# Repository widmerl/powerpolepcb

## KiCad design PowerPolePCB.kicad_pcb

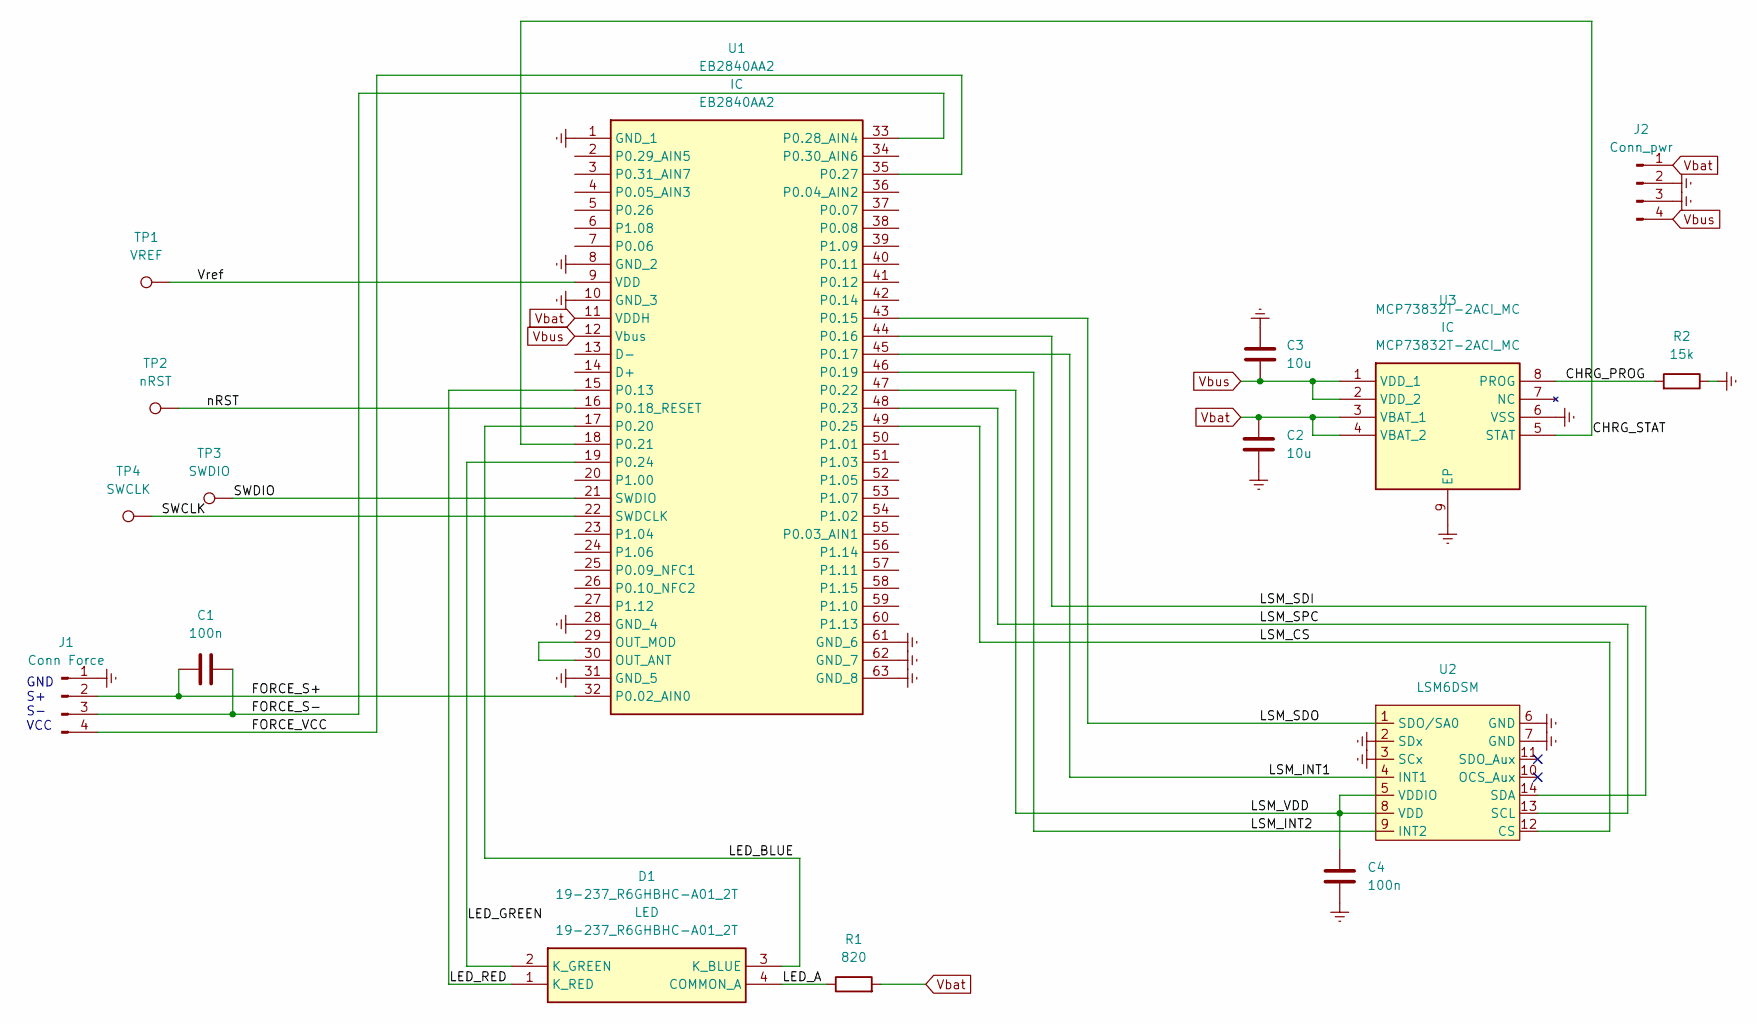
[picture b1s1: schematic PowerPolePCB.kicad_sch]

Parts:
C1, C4: 100n; C_0603_1608Metric; LCSC C14663
C2, C3: 10u; C_0603_1608Metric; LCSC C19702
D1: 19-237_R6GHBHC-A01_2T; 19237R6GHBHCA012T; Mouser Part Number 638-19237R6GHBHCA01
J1: Conn Force; PinHeader_1x04_P1.27mm_Vertical
J2: Conn_pwr; PinHeader_1x04_P1.27mm_Vertical
R1: 820; R_0603_1608Metric; LCSC C23253
R2: 15k; R_0603_1608Metric; LCSC C22809
TP1: VREF; uTP
TP2: nRST; uTP
TP3: SWDIO; uTP
TP4: SWCLK; uTP
U1: EB2840AA2; Manufacturer_Part_Number EB2840AA2
U2: LSM6DSM; LCSC C94048
U3: MCP73832T-2ACI_MC; SON50P300X200X100-9N-D; Mouser Part Number 579-MCP73832T-2ACIMC

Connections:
/CHRG_PROG: R2.2, U3.8 (PROG)
/CHRG_STAT: U1.18 (P0.21), U3.5 (STAT)
/FORCE_S+: C1.1, J1.2, U1.32 (P0.02_AIN0)
/FORCE_S-: C1.2, J1.3, U1.33 (P0.28_AIN4)
/FORCE_VCC: J1.4, U1.35 (P0.27)
/LED_A: D1.4 (COMMON_A), R1.1
/LED_BLUE: D1.3 (K_BLUE), U1.17 (P0.20)
/LED_GREEN: D1.2 (K_GREEN), U1.19 (P0.24)
/LED_RED: D1.1 (K_RED), U1.15 (P0.13)
/LSM_CS: U1.49 (P0.25), U2.12 (CS)
/LSM_INT1: U1.45 (P0.17), U2.4 (INT1)
/LSM_INT2: U1.46 (P0.19), U2.9 (INT2)
/LSM_SDI: U1.44 (P0.16), U2.14 (SDA)
/LSM_SDO: U1.43 (P0.15), U2.1 (SDO/SA0)
/LSM_SPC: U1.48 (P0.23), U2.13 (SCL)
/LSM_VDD: C4.1, U1.47 (P0.22), U2.5 (VDDIO), U2.8 (VDD)
/SWCLK: TP4.1, U1.22 (SWDCLK)
/SWDIO: TP3.1, U1.21 (SWDIO)
/Vref: TP1.1, U1.9 (VDD)
/nRST: TP2.1, U1.16 (P0.18_RESET)
Earth: C2.2, C3.1, C4.2, J1.1, J2.2, J2.3, R2.1, U1.1 (GND_1), U1.8 (GND_2), U1.10 (GND_3), U1.28 (GND_4), U1.31 (GND_5), U1.61 (GND_6), U1.62 (GND_7), U1.63 (GND_8), U2.2 (SDx), U2.3 (SCx), U2.6 (GND), U2.7 (GND), U3.6 (VSS), U3.9 (EP)
unnamed: U1.29 (OUT_MOD), U1.30 (OUT_ANT)
Vbat: C2.1, J2.1, R1.2, U1.11 (VDDH), U3.3 (VBAT_1), U3.4 (VBAT_2)
Vbus: C3.2, J2.4, U1.12 (Vbus), U3.1 (VDD_1), U3.2 (VDD_2)

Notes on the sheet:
GND S+ S- VCC

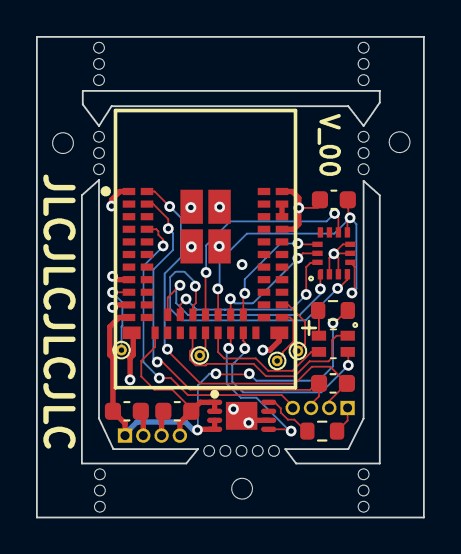
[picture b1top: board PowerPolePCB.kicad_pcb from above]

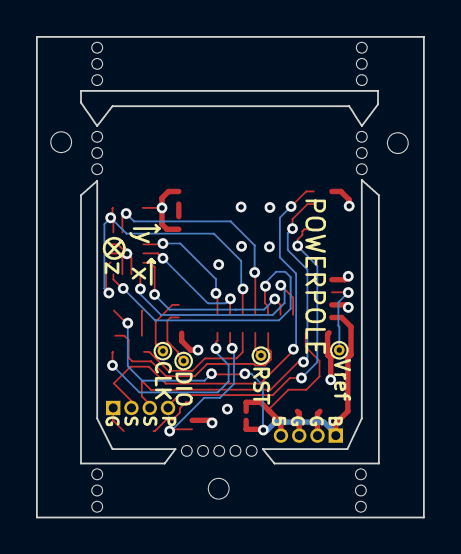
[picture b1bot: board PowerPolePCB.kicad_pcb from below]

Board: 4 copper layers, 21.5 x 26.7 mm, 26 parts (4 on the bottom side), 24 nets.

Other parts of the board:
MB1, MB2, MB3, MB4, MB5, MB6, MB7: mousebite
TH1, TH2, TH3: Tooling_hole_1.152; ToolingHole_1.152mm

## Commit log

2024-05-15 init
